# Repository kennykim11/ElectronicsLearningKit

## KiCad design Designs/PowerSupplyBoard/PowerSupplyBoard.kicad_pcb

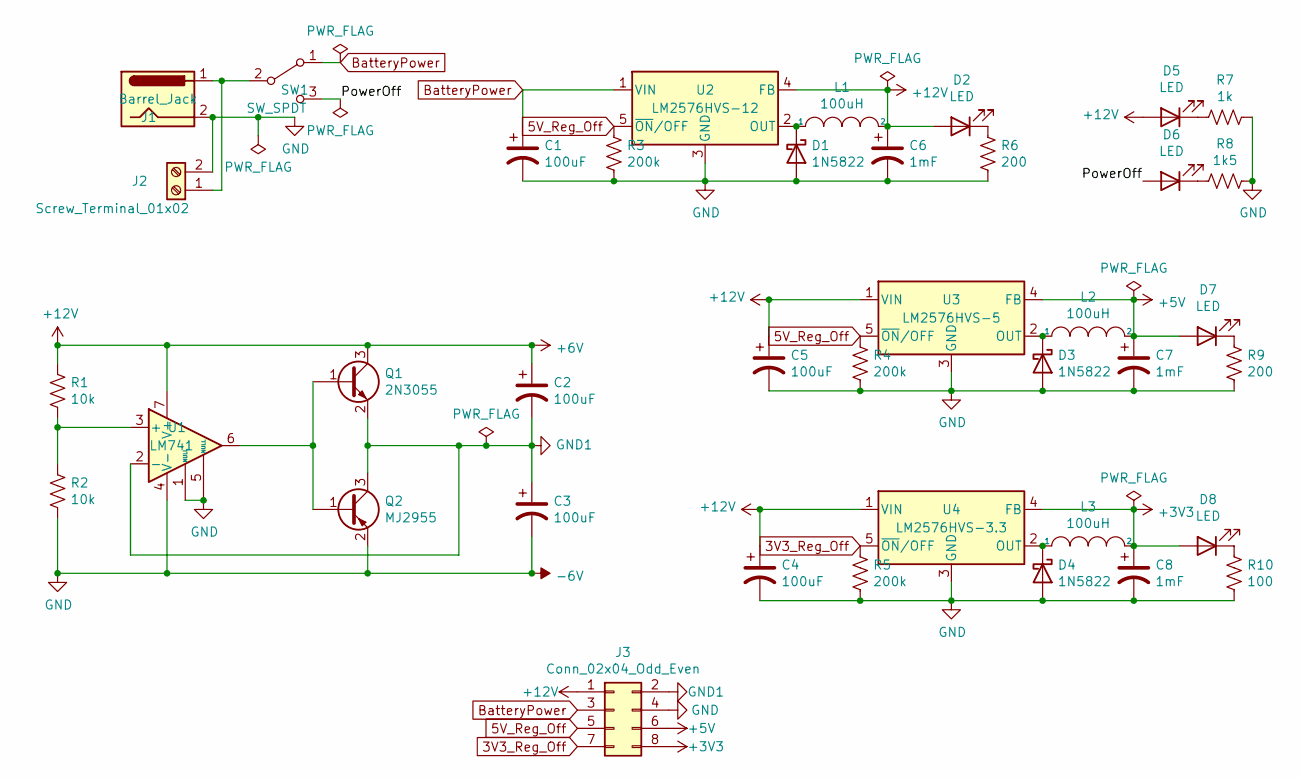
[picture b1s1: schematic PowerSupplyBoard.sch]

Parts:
C1, C2, C3, C4, C5: 100uF; CP_Radial_D8.0mm_P3.50mm
C6, C7, C8: 1mF; CP_Radial_D8.0mm_P3.50mm
D1, D3, D4: 1N5822; D_DO-201AD_P15.24mm_Horizontal
D2, D5, D6, D7, D8: LED; LED_D3.0mm
J1: Barrel_Jack; BarrelJack_CUI_PJ-063AH_Horizontal_CircularHoles
J2: Screw_Terminal_01x02; TerminalBlock_Phoenix_MKDS-1,5-2-5.08_1x02_P5.08mm_Horizont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
J3: Conn_02x04_Odd_Even; IDC-Header_2x04_P2.54mm_Vertical
L1, L2, L3: 100uH; L_Radial_D24.4mm_P23.90mm_muRATA_1400series
Q1: 2N3055; TO-3
Q2: MJ2955; TO-3
R1, R2: 10k; R_Axial_DIN0207_L6.3mm_D2.5mm_P15.24mm_Horizontal
R3, R4, R5: 200k; R_Axial_DIN0207_L6.3mm_D2.5mm_P15.24mm_Horizontal
R6, R9: 200; R_Axial_DIN0207_L6.3mm_D2.5mm_P15.24mm_Horizontal
R7: 1k; R_Axial_DIN0207_L6.3mm_D2.5mm_P15.24mm_Horizontal
R8: 1k5; R_Axial_DIN0207_L6.3mm_D2.5mm_P15.24mm_Horizontal
R10: 100; R_Axial_DIN0207_L6.3mm_D2.5mm_P15.24mm_Horizontal
SW1: SW_SPDT; SW_NKK_GW12LJP
U1: LM741; DIP-8_W7.62mm
U2: LM2576HVS-12; TO-263-5_TabPin3
U3: LM2576HVS-5; TO-263-5_TabPin3
U4: LM2576HVS-3.3; TO-263-5_TabPin3

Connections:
3V3_Reg_Off: J3.7, R5.1, U4.5 (~ON~/OFF)
5V_Reg_Off: J3.5, R3.1, R4.1, U2.5 (~ON~/OFF), U3.5 (~ON~/OFF)
+3V3: C8.1, D8.2 (A), J3.8, L3.2, U4.4 (FB)
+5V: C7.1, D7.2 (A), J3.6, L2.2, U3.4 (FB)
+12V: C2.1, C4.1, C5.1, C6.1, D2.2 (A), D5.2 (A), J3.1, L1.2, Q1.3 (C), R1.1, U1.7 (V+), U2.4 (FB), U3.1 (VIN), U4.1 (VIN)
-6V: C1.2, C3.2, C4.2, C5.2, C6.2, C7.2, C8.2, D1.2 (A), D3.2 (A), D4.2 (A), J1.2, J2.2, J3.4, Q2.2 (E), R2.2, R3.2, R4.2, R5.2, R6.2, R7.1, R8.1, R9.2, R10.2, U1.1 (NULL), U1.4 (V-), U1.5 (NULL), U2.3 (GND), U3.3 (GND), U4.3 (GND)
/PowerOff: D6.2 (A), SW1.3 (C)
BatteryPower: C1.1, J3.3, SW1.1 (A), U2.1 (VIN)
GND1: C2.2, C3.1, J3.2, Q1.2 (E), Q2.3 (C), U1.2 (-)
unnamed: D1.1 (K), L1.1, U2.2 (OUT)
unnamed: D2.1 (K), R6.1
unnamed: D3.1 (K), L2.1, U3.2 (OUT)
unnamed: D4.1 (K), L3.1, U4.2 (OUT)
unnamed: D5.1 (K), R7.2
unnamed: D6.1 (K), R8.2
unnamed: D7.1 (K), R9.1
unnamed: D8.1 (K), R10.1
unnamed: J1.1, J2.1, SW1.2 (B)
unnamed: Q1.1 (B), Q2.1 (B), U1.6
unnamed: R1.2, R2.1, U1.3 (+)

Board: 2 copper layers, 39 parts (0 on the bottom side), 20 nets, no tracks yet.

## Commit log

2021-04-11 Finished Power Board Schematic
